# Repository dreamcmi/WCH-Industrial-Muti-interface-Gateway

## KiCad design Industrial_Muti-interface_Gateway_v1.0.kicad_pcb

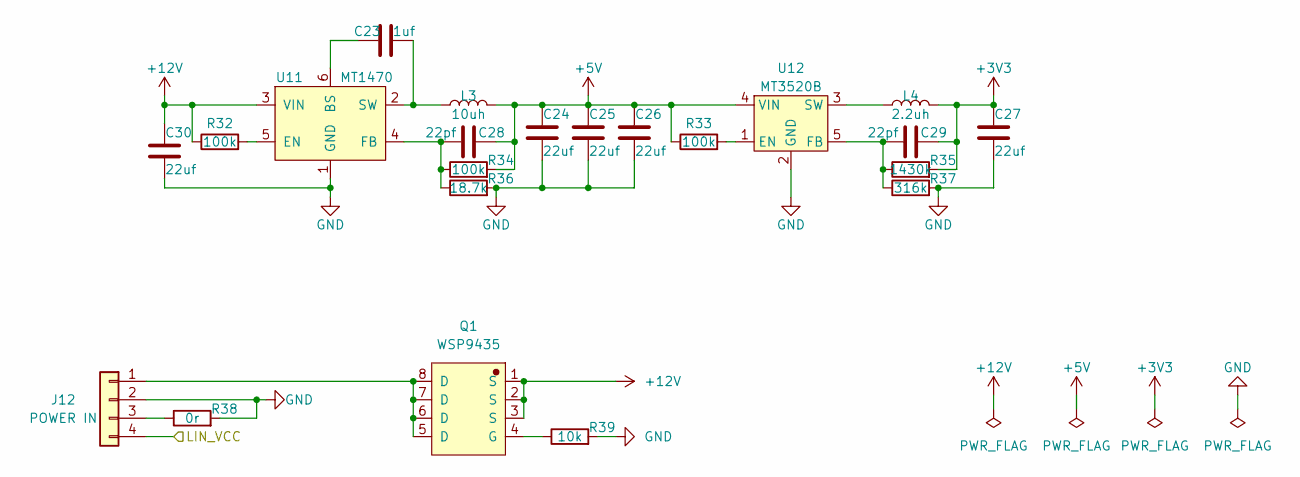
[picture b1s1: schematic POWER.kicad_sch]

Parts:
C23: 1uf; C_0402_1005Metric
C24, C25, C26, C27, C30: 22uf; C_0805_2012Metric
C28, C29: 22pf; C_0402_1005Metric
J12: POWER IN; PhoenixContact_MC_1,5_4-G-5.08_1x04_P5.08mm_Horizontal
L3: 10uh; IND-SMD_L2.5-W2.0
L4: 2.2uh; IND-SMD_L2.5-W2.0
Q1: WSP9435; SOP-8_3.9x4.9mm_P1.27mm
R32, R33, R34: 100k; R_0402_1005Metric
R35: 1430k; R_0402_1005Metric
R36: 18.7k; R_0402_1005Metric
R37: 316k; R_0402_1005Metric
R38: 0r; R_0402_1005Metric
R39: 10k; R_0402_1005Metric
U11: MT1470; SOT-23-6
U12: MT3520B; SOT-23-5

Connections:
+3V3: C27.1, C29.2, L4.2, R35.2; also elsewhere on the board
+5V: C24.1, C25.1, C26.1, C28.2, L3.2, R33.1, R34.2, U12.4 (VIN); also elsewhere on the board
+12V: C30.1, Q1.1 (S), Q1.2 (S), Q1.3 (S), R32.1, U11.3 (VIN)
/CH32V208/LIN_VCC: J12.4; also elsewhere on the board
GND: C24.2, C25.2, C26.2, C27.2, C30.2, J12.2, R36.2, R37.2, R38.2, R39.2, U11.1 (GND), U12.2 (GND); also elsewhere on the board
unnamed: C23.1, U11.6 (BS)
unnamed: C23.2, L3.1, U11.2 (SW)
unnamed: C28.1, R34.1, R36.1, U11.4 (FB)
unnamed: C29.1, R35.1, R37.1, U12.5 (FB)
unnamed: J12.1, Q1.5 (D), Q1.6 (D), Q1.7 (D), Q1.8 (D)
unnamed: J12.3, R38.1
unnamed: L4.1, U12.3 (SW)
unnamed: Q1.4 (G), R39.1
unnamed: R32.2, U11.5 (EN)
unnamed: R33.2, U12.1 (EN)

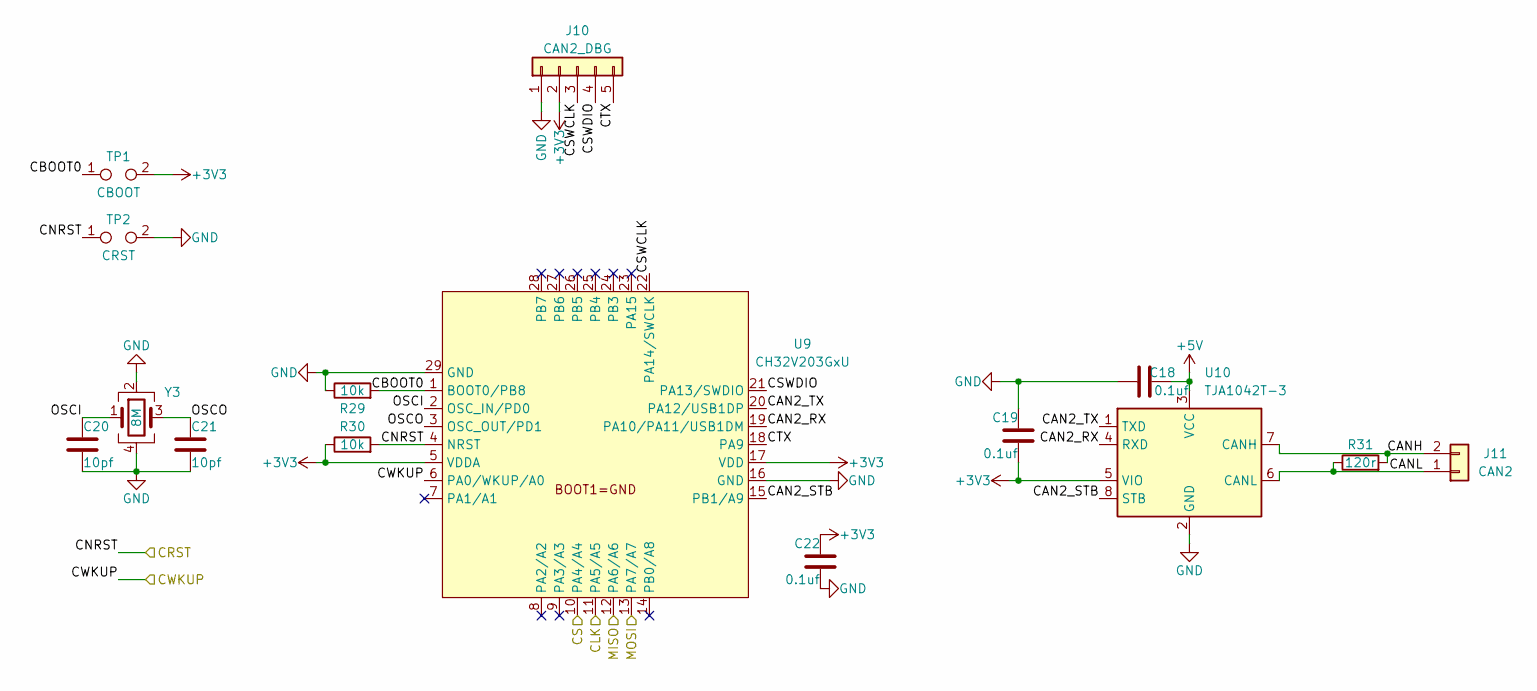
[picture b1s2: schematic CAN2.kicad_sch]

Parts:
C18, C19, C22: 0.1uf; C_0402_1005Metric
C20, C21: 10pf; C_0402_1005Metric
J10: CAN2_DBG; PinHeader_1x05_P2.54mm_Vertical
J11: CAN2; PhoenixContact_MC_1,5_2-G-5.08_1x02_P5.08mm_Horizontal
R29, R30: 10k; R_0402_1005Metric
R31: 120r; R_0603_1608Metric
TP1: CBOOT; SolderJumper-2_P1.3mm_Open_TrianglePad1.0x1.5mm
TP2: CRST; SolderJumper-2_P1.3mm_Open_TrianglePad1.0x1.5mm
U9: CH32V203GxU; QFN-28-1EP_4x4mm_P0.4mm_EP2.6x2.6mm
U10: TJA1042T-3; SOIC-8_3.9x4.9mm_P1.27mm
Y3: 8M; Crystal_SMD_3225-4Pin_3.2x2.5mm

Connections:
+3V3: C19.2, C22.1, J10.2, R30.1, TP1.2, U9.5 (VDDA), U9.17 (VDD), U10.5 (VIO); also elsewhere on the board
+5V: C18.2, U10.3 (VCC); also elsewhere on the board
/CAN2/CAN2_RX: U9.19 (PA10/PA11/USB1DM), U10.4 (RXD)
/CAN2/CAN2_STB: U9.15 (PB1/A9), U10.8 (STB)
/CAN2/CAN2_TX: U9.20 (PA12/USB1DP), U10.1 (TXD)
/CAN2/CANH: J11.2, R31.2, U10.7 (CANH)
/CAN2/CANL: J11.1, R31.1, U10.6 (CANL)
/CAN2/CBOOT0: R29.2, TP1.1, U9.1 (BOOT0/PB8)
/CAN2/CLK: U9.11 (PA5/A5); also elsewhere on the board
/CAN2/CNRST: R30.2, TP2.1, U9.4 (NRST); also elsewhere on the board
/CAN2/CS: U9.10 (PA4/A4); also elsewhere on the board
/CAN2/CSWCLK: J10.3, U9.22 (PA14/SWCLK)
/CAN2/CSWDIO: J10.4, U9.21 (PA13/SWDIO)
/CAN2/CTX: J10.5, U9.18 (PA9)
/CAN2/CWKUP: U9.6 (PA0/WKUP/A0); also elsewhere on the board
/CAN2/MISO: U9.12 (PA6/A6); also elsewhere on the board
/CAN2/MOSI: U9.13 (PA7/A7); also elsewhere on the board
/CAN2/OSCI: C20.1, U9.2 (OSC_IN/PD0), Y3.1
/CAN2/OSCO: C21.1, U9.3 (OSC_OUT/PD1), Y3.3
GND: C18.1, C19.1, C20.2, C21.2, C22.2, J10.1, R29.1, TP2.2, U9.16 (GND), U9.29 (GND), U10.2 (GND), Y3.2, Y3.4; also elsewhere on the board

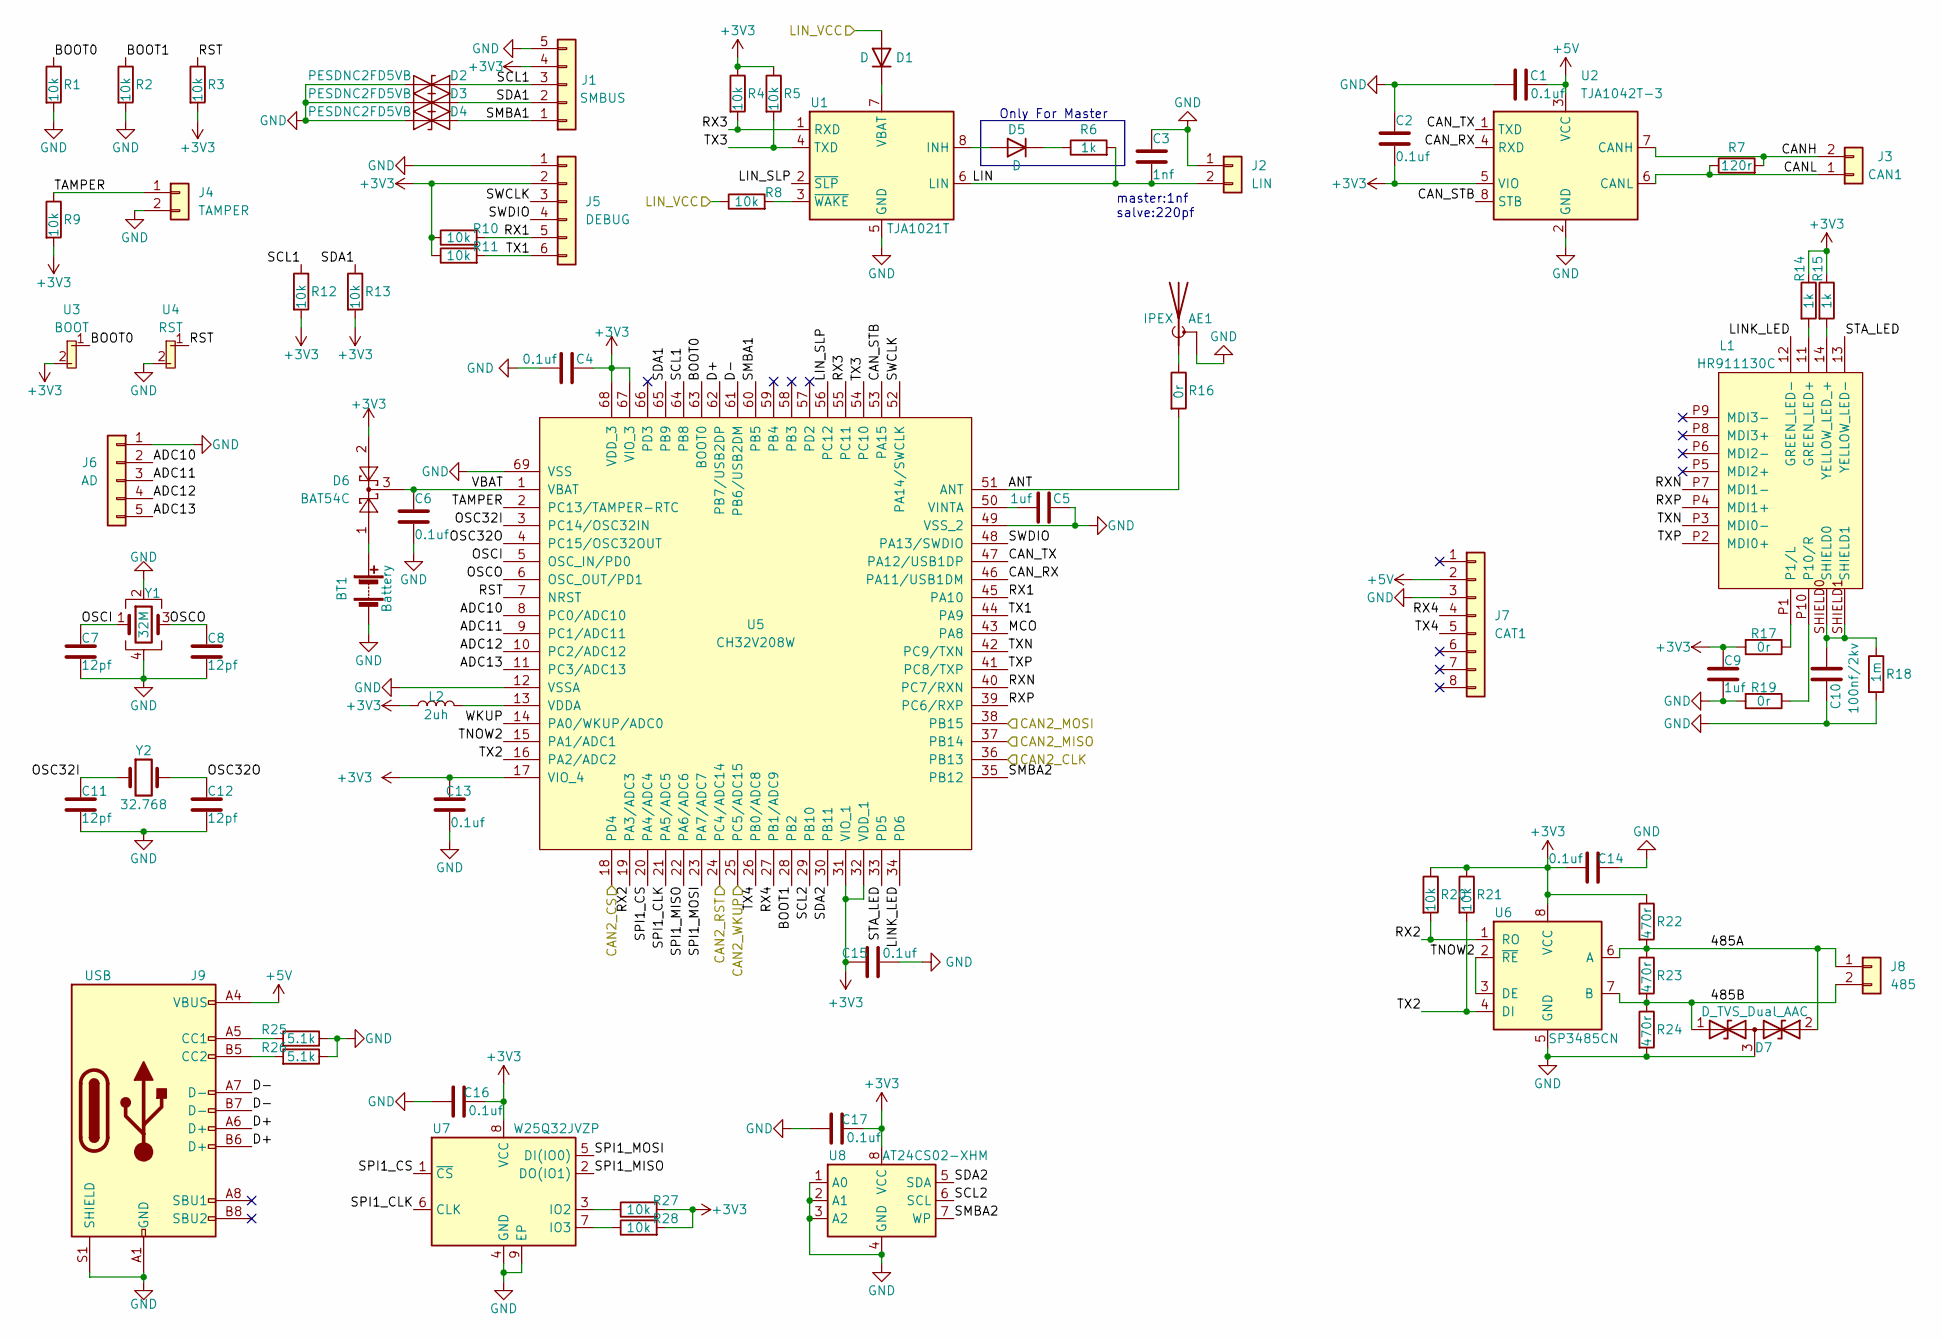
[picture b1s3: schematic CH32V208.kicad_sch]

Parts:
AE1: IPEX; IPEX-20279-001E
BT1: Battery; PinHeader_1x02_P2.54mm_Vertical
C1, C2, C4, C6, C13, C14, C15, C16, C17: 0.1uf; C_0402_1005Metric
C3: 1nf; C_0402_1005Metric
C5, C9: 1uf; C_0402_1005Metric
C7, C8, C11, C12: 12pf; C_0402_1005Metric
C10: 100nf/2kv; C_2220_5650Metric
D1, D5: D; D_SOD-523
D2, D3, D4: PESDNC2FD5VB; DFN1006-2L-BI
D6: BAT54C; SOT-23
D7: D_TVS_Dual_AAC; SOT-23
J1: SMBUS; JST_VH_B5P-VH_1x05_P3.96mm_Vertical
J2: LIN; PhoenixContact_MC_1,5_2-G-5.08_1x02_P5.08mm_Horizontal
J3: CAN1; PhoenixContact_MC_1,5_2-G-5.08_1x02_P5.08mm_Horizontal
J4: TAMPER; PinHeader_1x02_P2.54mm_Vertical
J5: DEBUG; PinHeader_1x06_P2.54mm_Vertical
J6: AD; PinHeader_1x05_P2.54mm_Vertical
J7: CAT1; PinHeader_1x08_P2.54mm_Vertical
J8: 485; PhoenixContact_MC_1,5_2-G-5.08_1x02_P5.08mm_Horizontal
J9: USB; USB_C_Receptacle_Palconn_UTC16-G
L1: HR911130C; RJ45-TH_HR911130C
L2: 2uh; L_0402_1005Metric
R1, R2, R3, R4, R5, R8, R9, R10, R11, R12, R13, R20, R21, R27, R28: 10k; R_0402_1005Metric
R6, R14, R15: 1k; R_0402_1005Metric
R7: 120r; R_0603_1608Metric
R16, R17: 0r; R_0402_1005Metric
R18: 1m; R_0603_1608Metric
R19: 0r; R_0603_1608Metric
R22, R23, R24: 470r; R_0402_1005Metric
R25, R26: 5.1k; R_0402_1005Metric
U1: TJA1021T; SOIC-8_3.9x4.9mm_P1.27mm
U2: TJA1042T-3; SOIC-8_3.9x4.9mm_P1.27mm
U3: BOOT; KEY-SMD_4P
U4: RST; KEY-SMD_4P
U5: CH32V208W; QFN-68-1EP_8x8mm_P0.4mm_EP5.2x5.2mm
U6: SP3485CN; SOIC-8_3.9x4.9mm_P1.27mm
U7: W25Q32JVZP; USON8_L2.0-W3.0-P0.50-BL-EP
U8: AT24CS02-XHM; TSSOP-8_4.4x3mm_P0.65mm
Y1: 32M; Crystal_SMD_3225-4Pin_3.2x2.5mm
Y2: 32.768; Crystal_SMD_3215-2Pin_3.2x1.5mm

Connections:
+3V3: C2.2, C4.2, C9.1, C13.2, C14.1, C15.2, C16.2, C17.2, D6.2, J1.4, J5.2, L2.1, R3.2, R4.1, R5.1, R9.2, R10.1, R11.1, R12.2, R13.2, R14.1, R15.1, R17.2, R20.1, R21.1, R22.1, R27.2, R28.2, U2.5 (VIO), U3.2, U5.17 (VIO_4), U5.31 (VIO_1), U5.32 (VDD_1), U5.67 (VIO_3), U5.68 (VDD_3), U6.8 (VCC), U7.8 (VCC), U8.8 (VCC); also elsewhere on the board
+5V: C1.2, J7.2, J9.A4 (VBUS), J9.A9 (VBUS), J9.B4 (VBUS), J9.B9 (VBUS), U2.3 (VCC); also elsewhere on the board
/CAN2/CLK: U5.36 (PB13); also elsewhere on the board
/CAN2/CNRST: U5.24 (PC4/ADC14); also elsewhere on the board
/CAN2/CS: U5.18 (PD4); also elsewhere on the board
/CAN2/CWKUP: U5.25 (PC5/ADC15); also elsewhere on the board
/CAN2/MISO: U5.37 (PB14); also elsewhere on the board
/CAN2/MOSI: U5.38 (PB15); also elsewhere on the board
/CH32V208/485A: D7.2 (A2), J8.1, R22.2, R23.1, U6.6 (A)
/CH32V208/485B: D7.1 (A1), J8.2, R23.2, R24.1, U6.7 (B)
/CH32V208/ADC10: J6.2, U5.8 (PC0/ADC10)
/CH32V208/ADC11: J6.3, U5.9 (PC1/ADC11)
/CH32V208/ADC12: J6.4, U5.10 (PC2/ADC12)
/CH32V208/ADC13: J6.5, U5.11 (PC3/ADC13)
/CH32V208/ANT: R16.2, U5.51 (ANT)
/CH32V208/BOOT0: R1.1, U3.1, U5.63 (BOOT0)
/CH32V208/BOOT1: R2.1, U5.28 (PB2)
/CH32V208/CANH: J3.2, R7.2, U2.7 (CANH)
/CH32V208/CANL: J3.1, R7.1, U2.6 (CANL)
/CH32V208/CAN_RX: U2.4 (RXD), U5.46 (PA11/USB1DM)
/CH32V208/CAN_STB: U2.8 (STB), U5.53 (PA15)
/CH32V208/CAN_TX: U2.1 (TXD), U5.47 (PA12/USB1DP)
/CH32V208/D+: J9.A6 (D+), J9.B6 (D+), U5.62 (PB7/USB2DP)
/CH32V208/D-: J9.A7 (D-), J9.B7 (D-), U5.61 (PB6/USB2DM)
/CH32V208/LIN: C3.2, J2.2, R6.2, U1.6 (LIN)
/CH32V208/LINK_LED: L1.12 (GREEN_LED-), U5.34 (PD6)
/CH32V208/LIN_SLP: U1.2 (~SLP), U5.56 (PC12)
/CH32V208/LIN_VCC: D1.2 (A), R8.1; also elsewhere on the board
/CH32V208/MCO: U5.43 (PA8)
/CH32V208/OSC32I: C11.1, U5.3 (PC14/OSC32IN), Y2.1
/CH32V208/OSC32O: C12.1, U5.4 (PC15/OSC32OUT), Y2.2
/CH32V208/OSCI: C7.1, U5.5 (OSC_IN/PD0), Y1.1
/CH32V208/OSCO: C8.1, U5.6 (OSC_OUT/PD1), Y1.3
/CH32V208/RST: R3.1, U4.1, U5.7 (NRST)
/CH32V208/RX1: J5.5, R10.2, U5.45 (PA10)
/CH32V208/RX2: R20.2, U5.19 (PA3/ADC3), U6.1 (RO)
/CH32V208/RX3: R4.2, U1.1 (RXD), U5.55 (PC11)
/CH32V208/RX4: J7.4, U5.27 (PB1/ADC9)
/CH32V208/RXN: L1.P7 (MDI1-), U5.40 (PC7/RXN)
/CH32V208/RXP: L1.P4 (MDI1+), U5.39 (PC6/RXP)
/CH32V208/SCL1: D2.2 (A2), J1.3, R12.1, U5.64 (PB8)
/CH32V208/SCL2: U5.29 (PB10), U8.6 (SCL)
/CH32V208/SDA1: D3.2 (A2), J1.2, R13.1, U5.65 (PB9)
/CH32V208/SDA2: U5.30 (PB11), U8.5 (SDA)
/CH32V208/SMBA1: D4.2 (A2), J1.1, U5.60 (PB5)
/CH32V208/SMBA2: U5.35 (PB12), U8.7 (WP)
/CH32V208/SPI1_CLK: U5.21 (PA5/ADC5), U7.6 (CLK)
/CH32V208/SPI1_CS: U5.20 (PA4/ADC4), U7.1 (~CS)
/CH32V208/SPI1_MISO: U5.22 (PA6/ADC6), U7.2 (DO(IO1))
/CH32V208/SPI1_MOSI: U5.23 (PA7/ADC7), U7.5 (DI(IO0))
/CH32V208/STA_LED: L1.13 (YELLOW_LED-), U5.33 (PD5)
/CH32V208/SWCLK: J5.3, U5.52 (PA14/SWCLK)
/CH32V208/SWDIO: J5.4, U5.48 (PA13/SWDIO)
/CH32V208/TAMPER: J4.1, R9.1, U5.2 (PC13/TAMPER-RTC)
/CH32V208/TNOW2: U5.15 (PA1/ADC1), U6.2 (~RE), U6.3 (DE)
/CH32V208/TX1: J5.6, R11.2, U5.44 (PA9)
/CH32V208/TX2: R21.2, U5.16 (PA2/ADC2), U6.4 (DI)
/CH32V208/TX3: R5.2, U1.4 (TXD), U5.54 (PC10)
/CH32V208/TX4: J7.5, U5.26 (PB0/ADC8)
/CH32V208/TXN: L1.P3 (MDI0-), U5.42 (PC9/TXN)
/CH32V208/TXP: L1.P2 (MDI0+), U5.41 (PC8/TXP)
/CH32V208/VBAT: C6.1, D6.3, U5.1 (VBAT)
/CH32V208/WKUP: U5.14 (PA0/WKUP/ADC0)
GND: AE1.2 (Shield), BT1.2 (-), C1.1, C2.1, C3.1, C4.1, C5.2, C6.2, C7.2, C8.2, C9.2, C10.2, C11.2, C12.2, C13.1, C14.2, C15.1, C16.1, C17.1, D2.1 (A1), D3.1 (A1), D4.1 (A1), D7.3 (common), J1.5, J2.1, J4.2, J5.1, J6.1, J7.3, J9.A1 (GND), J9.A12 (GND), J9.B1 (GND), J9.B12 (GND), J9.S1 (SHIELD), R1.2, R2.2, R18.2, R19.2, R24.2, R25.1, R26.1, U1.5 (GND), U2.2 (GND), U4.2, U5.12 (VSSA), U5.49 (VSS_2), U5.69 (VSS), U6.5 (GND), U7.4 (GND), U7.9 (EP), U8.1 (A0), U8.2 (A1), U8.3 (A2), U8.4 (GND), Y1.2, Y1.4; also elsewhere on the board
unnamed: AE1.1 (A), R16.1
unnamed: BT1.1 (+), D6.1
unnamed: C5.1, U5.50 (VINTA)
unnamed: C10.1, L1.SHIELD0, L1.SHIELD1, R18.1
unnamed: D1.1 (K), U1.7 (VBAT)
unnamed: D5.1 (K), R6.1
unnamed: D5.2 (A), U1.8 (INH)
unnamed: J9.A5 (CC1), R25.2
unnamed: J9.B5 (CC2), R26.2
unnamed: L1.11 (GREEN_LED+), R14.2
unnamed: L1.14 (YELLOW_LED_+), R15.2
unnamed: L1.P1 (P1/L), R17.1
unnamed: L1.P10 (P10/R), R19.1
unnamed: L2.2, U5.13 (VDDA)
unnamed: R8.2, U1.3 (~WAKE)
unnamed: R27.1, U7.3 (IO2)
unnamed: R28.1, U7.7 (IO3)

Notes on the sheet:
Only For Master
master:1nf salve:220pf

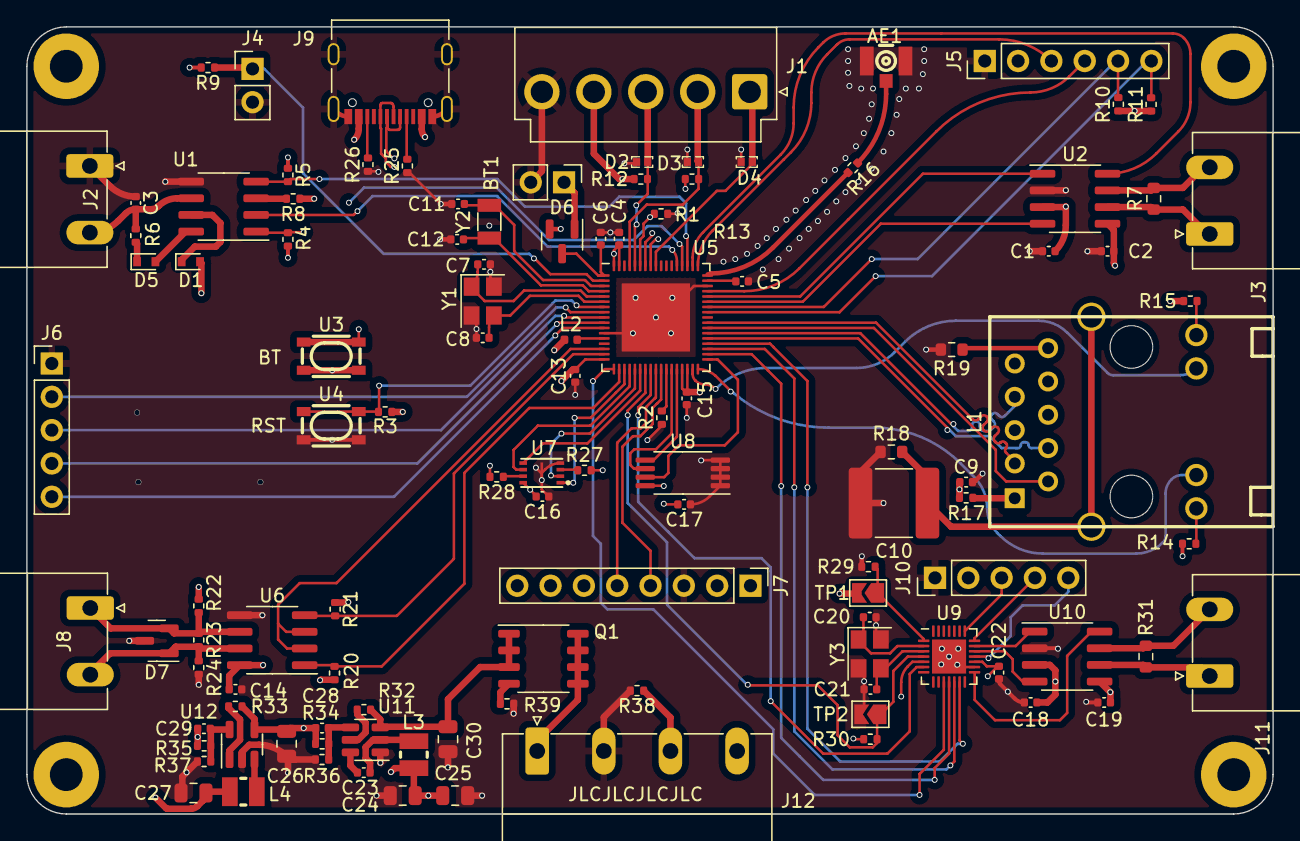
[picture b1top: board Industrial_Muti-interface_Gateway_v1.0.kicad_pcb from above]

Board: 4 copper layers, 95.0 x 60.0 mm, 112 parts (0 on the bottom side), 101 nets.

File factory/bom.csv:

Designator,Footprint,Quantity,Value,LCSC Part #
"R28,R9,R10,R4,R5,R27,R20,R30,R2,R39,R1,R29,R3,R13,R12,R8,R21,R11",R_0402_1005Metric,18,10k,
R37,R_0402_1005Metric,1,316k,
"C1,C2,C4,C6,C13,C14,C15,C16,C17,C18,C19,C22",C_0402_1005Metric,1,0.1uf,
"R6,R14,R15",R_0402_1005Metric,3,1k,
L4,IND-SMD_L2.5-W2.0,1,2.2uh,
"C27,C24,C25,C26,C30",C_0805_2012Metric,5,22uf,
"C23,C5,C9",C_0402_1005Metric,3,1uf,
"R38,R16,R17",R_0402_1005Metric,4,0r,
"R25,R26",R_0402_1005Metric,2,5.1k,
R36,R_0402_1005Metric,1,18.7k,
R18,R_0603_1608Metric,1,1m,
R35,R_0402_1005Metric,1,1.43m,
"R22,R23,R24",R_0402_1005Metric,3,470r,
"R32,R33,R34",R_0402_1005Metric,3,100k,
C3,C_0402_1005Metric,1,1nf,
L3,IND-SMD_L2.5-W2.0,1,10uh,
U5,QFN-68-1EP_8x8mm_P0.4mm_EP5.2x5.2mm,1,CH32V208W,
"R7,R31",R_0603_1608Metric,2,120r,
D6,SOT-23,1,BAT54C,
R19,R_0603_1608Metric,1,0R,

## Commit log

2023-02-28 init
2023-02-28 add readme
